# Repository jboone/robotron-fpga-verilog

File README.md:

# Robotron FPGA (Verilog)

Classic 1980s arcade video game implemented in an FPGA using Verilog, using some [custom video](hw/ecp5_analog_video), [sound](hw/ecp5_dac8), and controls interfacing hardware.

## Status

This project is stable. It has served the [Church of Robotron](https://churchofrobotron.com/) well during the [2019 Crowd Supply Teardown conference](https://www.crowdsupply.com/teardown/portland-2019) and the [2019 Portland Mini Maker Faire](https://omsi.edu/calendar/portland-mini-maker-faire-2019).

## Requirements

* Lattice [LFE5UM5G-85F-EVN FPGA evaluation board](https://www.latticesemi.com/products/developmentboardsandkits/ecp5evaluationboard): This is an economical way to get the largest ECP5 FPGA Lattice makes.
* Williams [Robotron: 2084 ROM binary files](https://duckduckgo.com/?q=robotron+2084+rom&t=hc&va=u&ia=web): These files are often used with MAME, the arcade emulator. CPU board ROM files are named "robotron.sb?", where "?" is "1" through "9" and "a" through "c". The sound board ROM file is named "robotron.snd". You'll also want a "nvram" file containing the desired contents of the game's 1K x 4 nonvolatile RAM.
* [Python](https://www.python.org/) 3.7 or newer: Used to transform ROM and PROM files into HEX files for inclusion in the FPGA bitstream.
* [Yosys](https://github.com/YosysHQ/yosys), [nextpnr](https://github.com/YosysHQ/nextpnr), [prjtrellis](https://github.com/YosysHQ/prjtrellis): Open-source FPGA toolchain required to produce a bitstream for the FPGA. If you don't want to build these from source code, give the [fpga-toolchain](https://github.com/YosysHQ/fpga-toolchain) releases a try. It's important to run recent versions of these tools, as they're advancing rapidly.
* [GHDL](https://github.com/ghdl/ghdl) and [GHDL-Yosys Plugin](https://github.com/ghdl/ghdl-yosys-plugin): These are required to build the [CPU68 6800/6801 VHDL core](rtl/cpu68.vhd), which is the processor in the sound board.
* [OpenOCD](http://openocd.org/): Required to program the development board over a USB cable.

## Notes

Once you have obtained ROM files, you need to put them in the `data/rom` directory. There are `MD5SUMS` and `SHA256SUMS` files in there that you can use to check the hashes for the ROMs you've obtained, to ensure they're the same ones I used. You can do this with either the `md5sum` or `sha256sum` programs, which are commonly pre-installed on UNIX/Linux-based computers:

```bash
$ cd data/rom
$ md5sum -c MD5SUMS
# Should report "OK" for all files listed in the MD5SUMS file.
$ sha256sum -c SHA256SUMS
# Should report "OK" for all files listed in the SHA256SUMS file.
```

To permit OpenOCD to program the ECP5 development board over USB, I had to create a `udev` rule on my Linux computer, as follows:

```bash
$ sudo vi /etc/udev/rules.d/53-lattice-ftdi.rules
# Add this to the file:
ATTRS{idVendor}=="0403", ATTRS{idProduct}=="6010", MODE="0660", GROUP="plugdev", TAG+="uaccess"
# And save and quit the editor.
# Then ask udev to re-read the rules.
$ sudo udevadm control --reload-rules && sudo udevadm trigger
# (Detach and) attach the development board USB cable.
```

With the project requirements installed on your computer, and the development board plugged into your computer, you should only need to do the following to start the game running:

```bash
$ cd robotron-fpga-verilog
$ make prog
```

## Project Hardware

This project includes two custom circuit boards which attach to the Lattice ECP5 development board. Both were made with [KiCAD 5](https://www.kicad.org/). Both are four-layer boards. The bill of materials is contained within the schematic, and can be exported from there. If you're located in North America, consider using the [OSH Park](https://oshpark.com/) four-layer service to fabricate your boards.

### [Analog Video Board](hw/ecp5_analog_video)

The analog video board takes DAC, synchronization, and configuration signals from the ECP5 FPGA and outputs composite video, S-video (separate chroma and luma), and VGA-style RGB.

To use the analog video board, the Lattice ECP5 development board needs a slight configuration change. The FPGA's VCCIO1 voltage supply changed from 2.5V to 3.3V, which involves removing resistor R100 and adding a 0 Ohm resistor as R105. Both resistors are located next to each other, in the very center of the bottom of the board. They appear to be "0603" resistors, which are thankfully manageable to solder for somebody experienced in surface-mount soldering, without fancy tools or a microscope.

### [Analog Audio DAC Board](hw/ecp5_dac8)

The analog audio DAC board takes audio sample data from the ECP5 FPGA and outputs an analog signal.

## Development Board Configuration

Before connecting any of the hardware in this project, please ensure the Lattice ECP5 development board is configured as shown in the following tables.

### Jumpers

| Jumper | State      | Function if Installed                                        |
|--------|------------|-------------------------------------------------------------|
| JP1    | Removed    | Holds FTDI FT2232H in reset (also stops 12MHz clock output?) |
| JP2    | Installed  | Supplies 12MHz from FTDI FT2232H to FPGA                     |
| JP3    | Removed    | Applies +12V to Arduino header pin J7.8                      |
| JP4    | Removed    | Applies +5V to Arduino header pin J7.5                       |
| JP5    | Removed    | Applies +3.3V to Arduino header pin J7.4                     |
| JP6    | Removed    | Applies +3.3V to Raspberry Pi header pins JP8.1 and JP8.17   |
| JP7    | Removed    | Applies +5V to Raspberry Pi header pins JP8.2 and JP8.4      |
| JP9    | Removed    | Disables 200MHz LVDS crystal oscillator                      |
| JP10   | Pins 1,2   | Sets VCCIO0 to +3.3V                                         |
| JP11   | Pins 1,2   | Sets VCCIO7 to +3.3V                                         |
| JP18   | Installed  | Connects 128Mb SPI flash CS# to FPGA CSSPIN                  |

### DIP Switch SW1

| Switch   | Position |
|----------|----------|
| TP       | ON       |
| CONFIG 0 | ON       |
| CONFIG 1 | OFF      |
| CONFIG 2 | ON       |

## Interfacing

### Game Controls

The mapping of FPGA pins on the evaluation board can be found in [ecp5evn.lpf](data/ecp5evn.lpf). All signals are active low (0 volts) with the FPGA providing weak pull-ups.

| Game Signal       | Evaluation Board Signal | FPGA Ball |
| ----------------- | ----------------------- | --------- |
| Move Up           | Header J5, pin 3        | H20       |
| Move Down         | Header J5, pin 11       | K19       |
| Move Left         | Header J5, pin 15       | K20       |
| Move Right        | Header J5, pin 7        | K18       |
| Fire Up           | Header J5, pin 4        | G19       |
| Fire Down         | Header J5, pin 12       | J19       |
| Fire Left         | Header J5, pin 16       | J20       |
| Fire Right        | Header J5, pin 8        | J18       |
| Player Start 1-Up | Header J5, pin 19       | G20       |
| Left Coin Detect  | Push button SW4         | P4        |

Other game signals are set to constant values inside [top.v](rtl/top.v). If you need them, you'll need to do some alteration of the Verilog and .lpf files.

To start a game, you first need to add one or more coins (press push button SW4), then press the player start 1-up button (pulling header J4 pin 19 to ground). And off you go!

### Raspberry Pi Event Reporting

The Lattice ECP5 development board has a [Raspberry Pi](https://www.raspberrypi.org/) [GPIO header](https://www.raspberrypi.org/documentation/usage/gpio/README.md) on it, which we use to send game events to the Raspberry Pi serial port "RX" (GPIO15) signal on header pin 10. The baud rate is approximately 115,200 baud (12 MHz / 104) as determined in [uart_tx.v](rtl/uart_tx.v), and uses eight data bits, one start bit, one stop bit, and no parity. The events are transmitted by [events.v](rtl/events.v), but are detected and captured within [cpu.v](rtl/cpu.v). Have a look at the [simple Python event decoder example](sw/serial-decoder.py) for more details.

## Future Plans

I've gotten hooked on writing my FPGA project hardware descriptions in [nMigen](https://github.com/nmigen/nmigen), so would like to reimplement some or all of the project using nMigen. It should become significantly more concise and less fragile to work with than Verilog code.

## Reference Material

These documents served me well during development of this project.

* [Sean Riddle](http://seanriddle.com/) - Williams arcade machine information, including Robotron: 2084.
    * [Hardware overview](http://seanriddle.com/willhard.html)
    * [Memory map](http://seanriddle.com/memmap.gif)
    * [Processor and video timing](http://seanriddle.com/timing.html)
    * [BLTter description and test code](http://seanriddle.com/blittest.html)
* [Robotron-2084](http://www.robotron-2084.co.uk/) - Williams arcade machine official documentation.
    * [Robotron schematics and instruction manuals](http://www.robotron-2084.co.uk/manualsrobotron.html)
    * [Defender "later series" theory of operation](http://www.robotron-2084.co.uk/manualsdefender.html),
      interesting because the Robotron and Defender hardware is quite
      similar.
* Documentation for various ICs in the original Robotron: 2084 machine.
    * [MC6809E microprocessor datasheet](http://www.classiccmp.org/dunfield/r/6809e.pdf)
    * [MC6809E microprocessor programming manual](http://www.classiccmp.org/dunfield/r/6809prog.pdf)
    * [DM9316 Synchronous 4-Bit Binary Counter](http://www.ti.com/product/dm9316)
    * National Semiconductor(?) DM7489 64-bit random access read/write memory
    (no good reference)
    * [Harris HM-7641 512 x 8 PROM](http://www.bitsavers.org/pdf/harris/_dataBooks/1978_Harris_Memory_Vol1.pdf) (page 2-35)
    * [Harris HM-6514 1024 x 4 CMOS RAM](http://www.bitsavers.org/pdf/harris/_dataBooks/1978_Harris_Memory_Vol1.pdf) (page 3-49)
    * [Mostek MK4116 16,384 x 1 bit dynamic RAM](http://hardware.speccy.org/datasheet/MK4116.pdf)
    * [Signetics 8T97 hex buffer](http://www.bitsavers.org/pdf/signetics/_dataBooks/1977_Bipolar_Microprocessor.pdf) (page 96)
    * [Various 74-series logic ICs](http://www.ti.com/lsds/ti/logic/home_overview.page)

## License

The open-source license for this project is yet to be determined. Stay tuned.

## Contributing

Contributions are welcome!

Please respect Williams Electronics' copyright and do not post any files built with or containing their ROM code.

## Contact

Jared Boone <jared@sharebrained.com>

[ShareBrained Technology, Inc.](http://www.sharebrained.com/)

The latest version of this repository can be found at https://github.com/jboone/robotron-fpga-verilog

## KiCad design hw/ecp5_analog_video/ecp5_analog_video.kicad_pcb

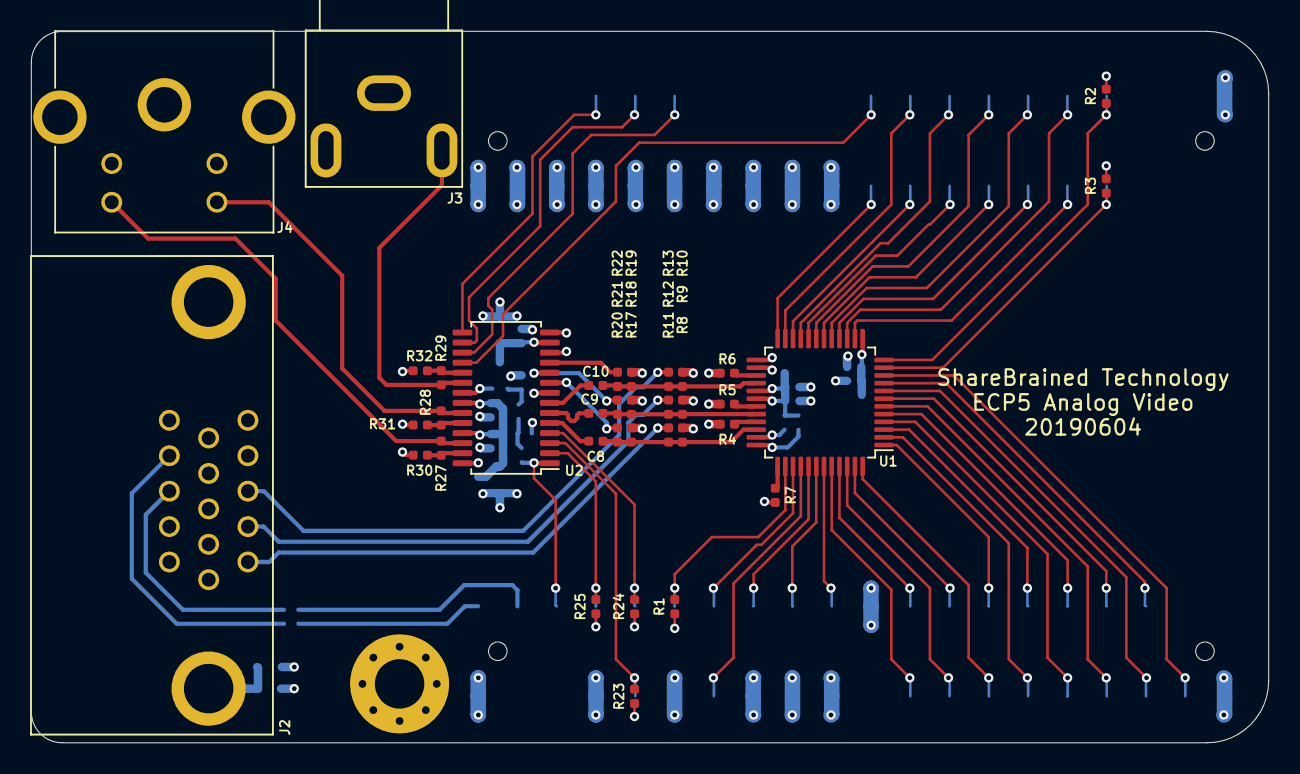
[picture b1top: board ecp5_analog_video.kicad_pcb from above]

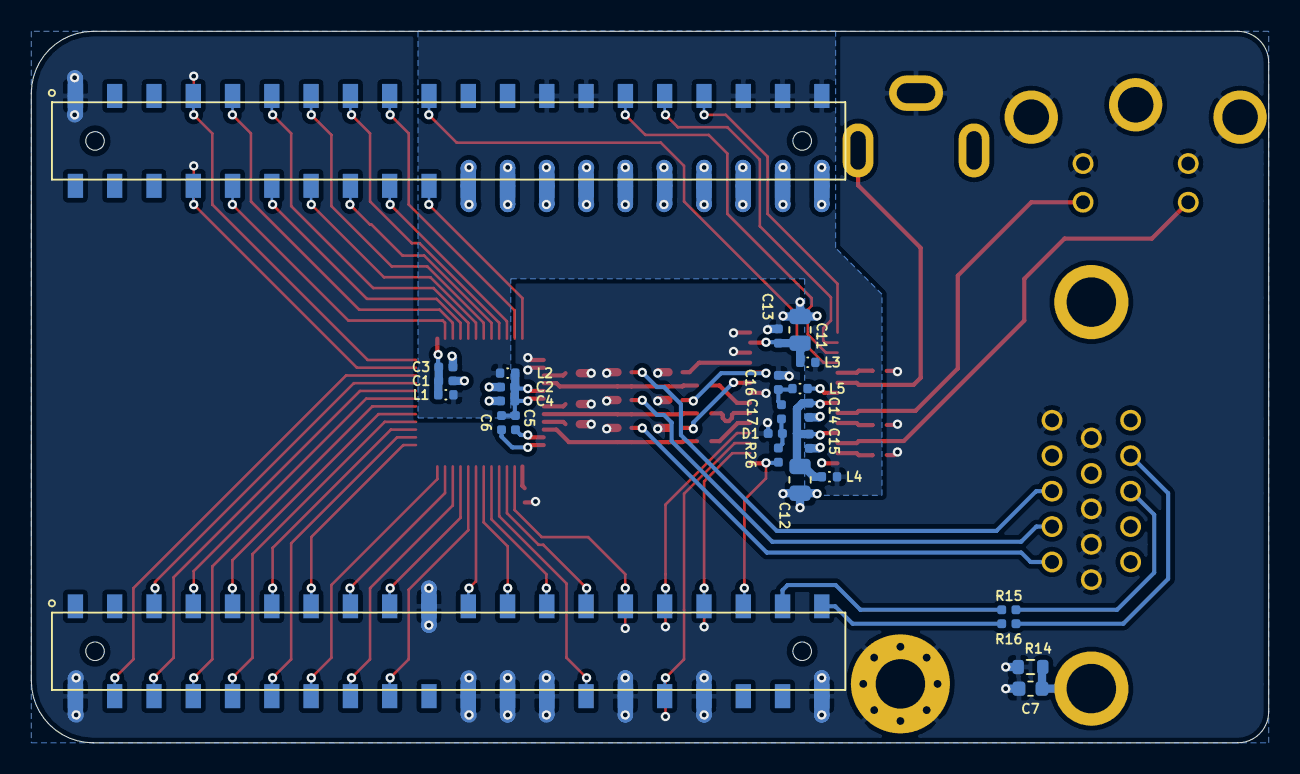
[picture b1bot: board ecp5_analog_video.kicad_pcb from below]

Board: 4 copper layers, 80.0 x 46.0 mm, 62 parts (25 on the bottom side), 80 nets.

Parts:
C1, C2, C5, C6, C8, C9, C10, C13, C14, C15: 100N; IPC_CAPC100X50X55L25N
C3, C4: 10N; IPC_CAPC100X50X55L25N
C7: 1N; IPC_CAPC160X80X90L35N
C11, C12: 10U; IPC_CAPC200X125X135L45N
C16: 18P; IPC_CAPC100X50X55L25N
C17: 9P; IPC_CAPC100X50X55L25N
D1: 1N4148; IPC_RESC100X50X40L25N
H1: MountingHole_Pad; MountingHole_3.2mm_M3_Pad_Via
J1: ECP5EVB_VERSA
J2: DB15_Female_HighDensity_MountingHoles; ICD15S13E4GX
J3: Barrel_Jack_Switch; PJRAN1X1U__X
J4: Mini-DIN-4; MD-40SMK
L1, L2, L3, L4: L_Small; IPC_INDC100X50X60L20N
L5: 68U; IPC_INDC100X50X60L20N
R1, R2, R3, R23, R24, R25: 100K; IPC_RESC100X50X40L25N
R4, R5, R6, R8, R9, R10, R17, R18, R19, R20, R21, R22: 75R; IPC_RESC100X50X40L25N
R7: 536R; IPC_RESC100X50X40L25N
R11, R12, R13: 0R; IPC_RESC100X50X40L25N
R14: 1M; IPC_RESC160X80X55L25N
R15, R16: 100R; IPC_RESC100X50X40L25N
R26: 47K; IPC_RESC100X50X40L25N
R27, R28, R29: 374R; IPC_RESC100X50X40L25N
R30, R31, R32: 300R; IPC_RESC100X50X40L25N
U1: ADV7123; IPC_QFP48P50_900X900X160L60X22N
U2: AD723; IPC_SOP28P65_970X637X110L60X24N

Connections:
/DAC_B0: J1.J39.10, U1.14
/DAC_B1: J1.J39.09, U1.15
/DAC_B2: J1.J39.12, U1.16
/DAC_B3: J1.J39.11, U1.17
/DAC_B4: J1.J39.14, U1.18
/DAC_B5: J1.J39.13, U1.19
/DAC_B6: J1.J39.16, U1.20
/DAC_B7: J1.J39.15, U1.21
/DAC_B8: J1.J39.18, U1.22
/DAC_B9: J1.J39.17, U1.23
/DAC_BLANK#: J1.J39.08, R3.1, U1.11
/DAC_CLOCK: J1.J39.20, U1.24
/DAC_G0: J1.J40.13, U1.1
/DAC_G1: J1.J40.12, U1.2
/DAC_G2: J1.J40.11, U1.3
/DAC_G3: J1.J40.10, U1.4
/DAC_G4: J1.J40.09, U1.5
/DAC_G5: J1.J40.08, U1.6
/DAC_G6: J1.J40.07, U1.7
/DAC_G7: J1.J40.06, U1.8
/DAC_G8: J1.J40.05, U1.9
/DAC_G9: J1.J40.04, U1.10
/DAC_IOB: C10.2, R10.1, R13.1, R19.1, R22.1, U1.28
/DAC_IOG: C9.2, R9.1, R12.1, R18.1, R21.1, U1.32
/DAC_IOR: C8.2, R8.1, R11.1, R17.1, R20.1, U1.34
/DAC_PSAVE#: J1.J40.29, R1.1, U1.38
/DAC_R0: J1.J40.27, U1.39
/DAC_R1: J1.J40.28, U1.40
/DAC_R2: J1.J40.25, U1.41
/DAC_R3: J1.J40.23, U1.42
/DAC_R4: J1.J40.21, U1.43
/DAC_R5: J1.J40.18, U1.44
/DAC_R6: J1.J40.17, U1.45
/DAC_R7: J1.J40.16, U1.46
/DAC_R8: J1.J40.15, U1.47
/DAC_R9: J1.J40.14, U1.48
/DAC_SYNC#: J1.J39.07, R2.1, U1.12
/ENC_4FSC: J1.J39.29, U2.17
/ENC_CE: J1.J40.32, R23.1, U2.3
/ENC_HSYNC: J1.J39.33, U2.15
/ENC_SA: J1.J40.33, R25.1, U2.2
/ENC_STND: J1.J40.35, R26.1, U2.1
/ENC_TERM: J1.J40.31, R24.1, U2.4
/ENC_TVDET: J1.J39.19, U2.18
/ENC_VSYNC: J1.J39.31, U2.16
/VGA_B: J2.3, R13.2
/VGA_G: J2.2, R12.2
/VGA_HSYNC: J1.J40.37, R15.2
/VGA_R: J2.1, R11.2
/VGA_VSYNC: J1.J40.39, R16.2
GND: C1.1, C2.1, C3.1, C4.1, C7.1, C11.1, C12.1, C13.1, C14.1, C15.1, C16.1, D1.1, H1.1, J1.J39.01, J1.J39.22, J1.J39.24, J1.J39.26, J1.J39.28, J1.J39.30, J1.J39.32, J1.J39.34, J1.J39.36, J1.J39.38, J1.J39.40, J1.J40.02, J1.J40.19, J1.J40.22, J1.J40.24, J1.J40.26, J1.J40.30, J1.J40.34, J1.J40.40, J2.5, J2.6, J2.7, J2.8, J2.10, J3.1, J4.1, J4.2, J4.SH, R1.2, R2.2, R3.2, R4.2, R5.2, R6.2, R7.1, R8.2, R9.2, R10.2, R14.1, R17.2, R18.2, R19.2, R23.2, R24.2, R25.2, R30.2, R31.2, R32.2, U1.25, U1.26, U2.8, U2.12, U2.14, U2.28
unnamed: C1.2, C3.2, L1.2, U1.13
unnamed: C2.2, C4.2, C5.1, C6.1, L2.2, U1.29, U1.30
unnamed: C5.2, U1.35
unnamed: C6.2, U1.36
unnamed: C7.2, J2.0, R14.2
unnamed: C8.1, U2.5
unnamed: C9.1, U2.6
unnamed: C10.1, U2.7
unnamed: C11.2, C13.2, L3.2, U2.13
unnamed: C12.2, C14.2, C15.2, L4.2, U2.22, U2.25
unnamed: C16.2, C17.2, L5.2
unnamed: C17.1, D1.2, R26.2
unnamed: J2.13, R15.1
unnamed: J2.14, R16.1
unnamed: J3.2, R29.1, U2.20
unnamed: J4.3, R27.1, U2.26
unnamed: J4.4, R28.1, U2.23
unnamed: L5.1, U2.21
unnamed: R4.1, U1.33
unnamed: R5.1, U1.31
unnamed: R6.1, U1.27
unnamed: R7.2, U1.37
unnamed: R20.2, U2.9
unnamed: R21.2, U2.10
unnamed: R22.2, U2.11
unnamed: R27.2, R30.1, U2.27
unnamed: R28.2, R31.1, U2.24
unnamed: R29.2, R32.1, U2.19
VAA: J1.J39.25, J1.J39.27, J1.J39.35, J1.J39.37, J1.J39.39, L1.1, L2.1, L3.1, L4.1

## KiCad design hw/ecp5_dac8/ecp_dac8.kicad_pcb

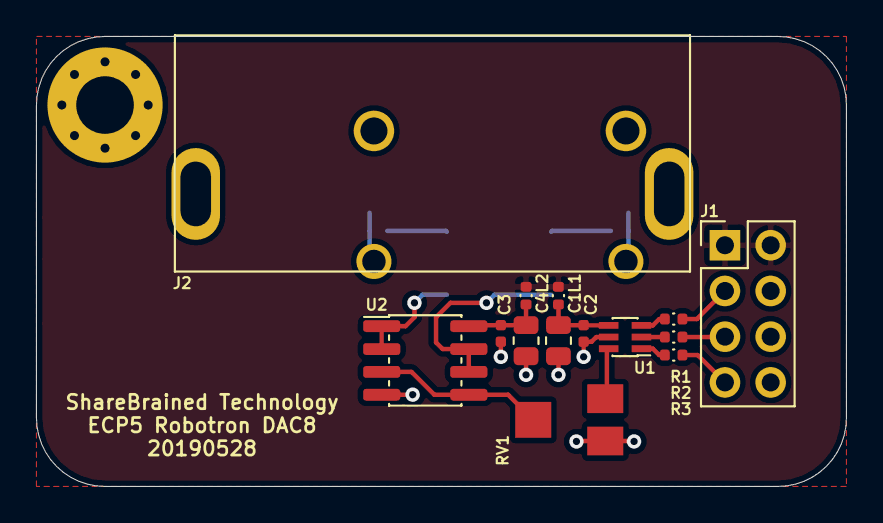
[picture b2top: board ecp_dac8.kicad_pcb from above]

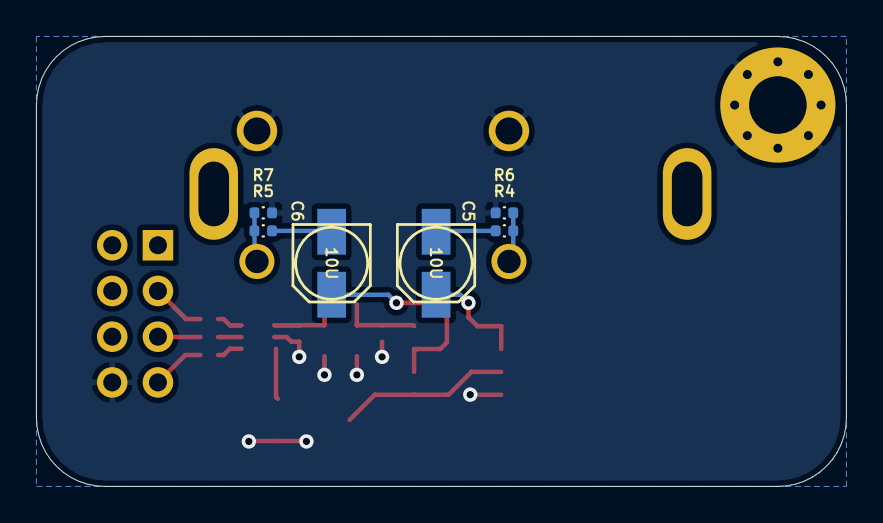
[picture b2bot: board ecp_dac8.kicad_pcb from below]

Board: 2 copper layers, 45.0 x 25.0 mm, 21 parts (6 on the bottom side), 18 nets.

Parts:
C1, C4: 10U; IPC_CAPC200X125X135L45N
C2, C3: 100N; IPC_CAPC100X50X55L25N
C5, C6: 10U; IPC_CAPAE430X540N
H1: MountingHole_Pad; MountingHole_3.2mm_M3_Pad_Via
J1: Conn_02x04_Odd_Even; PinHeader_2x04_P2.54mm_Vertical
J2: Conn_Coaxial_x2_Isolated; PJRAS2X1S0_X
L1, L2: FB; IPC_INDC100X50X60L20N
R1, R2, R3, R4, R5: 150R; IPC_INDC100X50X60L20N
R6, R7: 100K; IPC_INDC100X50X60L20N
RV1: 10K; NIDEC_ST-4EA
U1: AD5621BKSZ; IPC_SOT23-6P65_210X110L36X22N
U2: LME49721MAX; IPC_SOIC8P127_490X599X175L84X41N

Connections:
/L16: J1.7, R3.1
/L19: J1.3, R1.1
/L20: J1.5, R2.1
/SCLK: R2.2, U1.2
/SDIN: R1.2, U1.3
/SYNC#: R3.2, U1.1
GND: C1.2, C2.2, C3.2, C4.2, H1.1, J1.8, J2.2, J2.4, R6.2, R7.2, RV1.3, U1.5, U2.4
unnamed: C1.1, C2.1, L1.2, U1.4
unnamed: C3.1, C4.1, L2.1, U2.8
unnamed: C5.1, U2.1, U2.2
unnamed: C5.2, R4.2
unnamed: C6.1, U2.6, U2.7
unnamed: C6.2, R5.2
unnamed: J2.1, R5.1, R7.1
unnamed: J2.3, R4.1, R6.1
unnamed: RV1.1, U1.6
unnamed: RV1.2, U2.3, U2.5
VCC: J1.1, J1.2, L1.1, L2.2

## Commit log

2019-06-05 Initial commit of actual stuff.
2019-06-18 Comment out unused signals.
2019-06-18 Change some signals to 3.3V VCCIO, renumber DIP switches.
2019-06-18 Add timing declarations that Lattice Diamond wants.
2019-06-18 Rename button signal disable button and 12MHz clock internal pull-ups.
2019-06-18 Rename signals on J8 for use with audio DAC.
2019-06-18 Take one Raspberry Pi GPIO pin for events TX.
2019-06-18 Declare signals on J5 as joystick move/fire inputs and player 1 start button.
2019-06-18 Add Diamond delcaration of SPI programming passthrough.
2019-06-18 Make: specify top module.
2019-06-18 Make: Modify mkrom.py to accept args, use to generate sound ROM.
2019-06-18 CPU: Minor initialization cut-and-paste oops.
2019-06-18 Diamond: Verilog syntax tweaks (no ++ operator?).
2019-06-18 Clock generator: Improve readability of one-hot phase signal value.
2019-06-18 SC1: A little less bit-width syntax noise.
2019-06-18 HDL: Got impatient, committed everything else...
    Implemented sound.
    Changed some syntax to make Diamond happy.
    Rebaked HSync, VSync, added DAC+composite output.
    Exposed CPU state to add events output.
    Fixed some video palette clocking problems.
    Added joysticks and player 1 inputs.
2019-06-18 Testbench: Events to UART output.
2019-06-18 Tool: Quick and dirty NVRAM checksum calculator.
2019-06-18 Sample Python serial events dispatcher.
2019-07-15 6800: Extend some instructions to match cycle count in data sheet.
    This makes the pitch of sound effects much closer to the original game.
2019-07-15 Sound: Expose diagnostic signal, a few syntax tweaks.
    Diagnostic is available on original hardware as a push button that asserts NMI# and produces a sequence of test sounds.
2019-07-15 Sound: Fix direction of PB, HAND signals.
2019-07-15 Boards: Update component values and part numbers.
2019-07-15 DAC8 PCB: Correct package category for some resistors.
2019-07-15 Video PCB: Note about ECP5 initial I/O state.
2019-07-15 Sim: Add sound testbench.
2021-05-14 Add missing source files, sound file dependency
2021-05-14 Add GHDL and Yosys plugin requirement to process VHDL sound CPU file
2021-05-14 Remove some dead Verilog code.
2021-05-14 Add OpenOCD requirement and udev rule note.
2021-05-14 Adjust TRELLIS path to a more common scenario.
    ...at least for the way I'm doing things now.
2021-05-14 Add hashes for expected ROM files.
2021-05-14 A ton of README improvements and clean-up.
2021-05-14 Added details about the video and audio board designs.
2021-05-14 Analog video board: update some resistor values.
2021-05-14 Lots more README documentation
    Links to the hardware (circuit boards) portion of the project.
    Instructions on how to build and load the bitstream on the development board.
    Game control pinout.
    Raspberry Pi interface info.
    Future project plans.
    Clean up bullet-points formatting.
